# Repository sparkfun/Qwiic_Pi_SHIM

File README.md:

SparkFun Qwiic SHIM for Raspberry Pi
========================================

[*SparkFun Qwiic SHIM for Raspberry Pi (15794)*](https://www.sparkfun.com/products/15794)

A small breakout board to add a qwiic connector to your Raspberry Pi 40pin header. SHIM (Shove Hardware In the Middle).

Repository Contents
-------------------

* **/Hardware** - Eagle design files (.brd, .sch)

Documentation
--------------
* **[Hookup Guide](https://learn.sparkfun.com/tutorials/qwiic-shim-for-raspberry-pi-hookup-guide)** - Basic hookup guide for the SparkFun Qwiic SHIM for Raspberry Pi. 

License Information
-------------------

This product is _**open source**_! 

Please review the LICENSE.md file for license information. 

If you have any questions or concerns on licensing, please contact technical support on our [SparkFun forums](https://forum.sparkfun.com/viewforum.php?f=152).

Distributed as-is; no warranty is given.

- Your friends at SparkFun.

_<COLLABORATION CREDIT>_

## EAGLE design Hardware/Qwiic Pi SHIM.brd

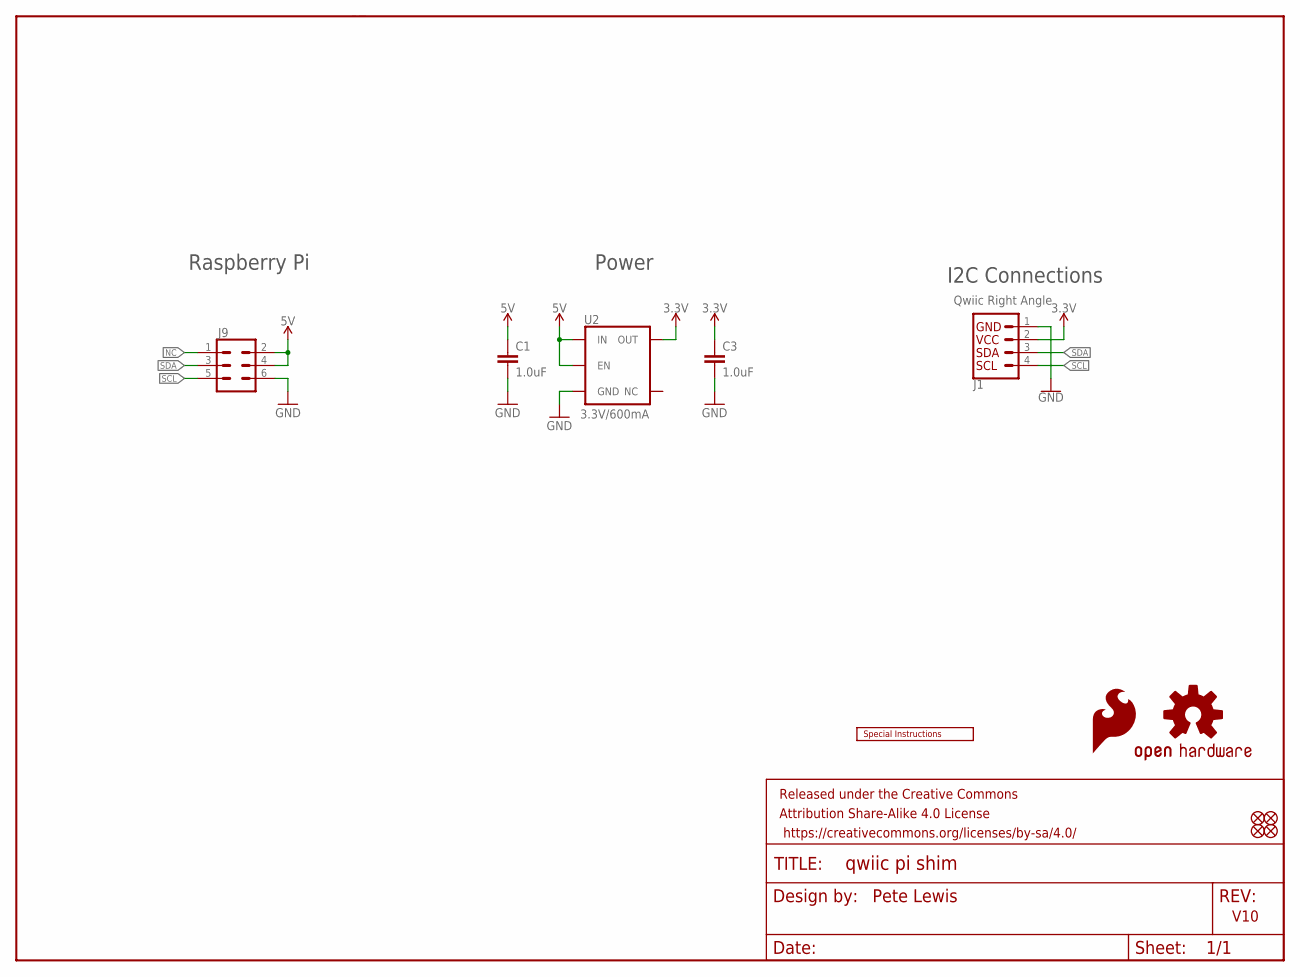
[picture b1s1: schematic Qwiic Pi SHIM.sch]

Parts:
C1, C3: 1.0uF; 0603
FD1, FD2, FD3, FD4: FIDUCIALUFIDUCIAL; FIDUCIAL-MICRO
FRAME1: FRAME-LETTER; CREATIVE_COMMONS
J1: Qwiic Right Angle; 1X04_1MM_RA
J9: SPARKFUN-CONNECTORS_CONN_03X2PISHIM_LOCK_SLOTS; SPARKFUN-CONNECTORS_2X3-NS_PISHIM_LOCKING_SLOTS
LOGO1: OSHW-LOGOMINI; OSHW-LOGO-MINI
U2: 3.3V/600mA; SOT23-5
U$1: SFE_LOGO_FLAME.1_INCH; SFE_LOGO_FLAME_.1
U$4: SPECIAL_INSTRUCTIONS-ORDERING; ORDERING_INSTRUCTIONS

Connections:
3.3V: C3.1, J1.2, U2.5 (OUT)
5V: C1.1, J9.2, J9.4, U2.1 (IN), U2.3 (EN)
GND: C1.2, C3.2, J1.1, J9.6, U2.2 (GND)
NC: J9.1
SCL: J1.4, J9.5
SDA: J1.3, J9.3

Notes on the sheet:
Pete Lewis
Raspberry Pi
V10
I2C Connections
Power

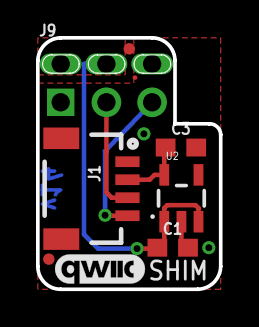
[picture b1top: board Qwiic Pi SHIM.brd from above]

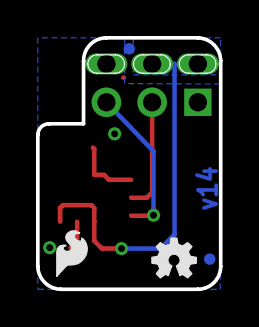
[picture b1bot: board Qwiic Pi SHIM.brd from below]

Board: 2 copper layers, 10.2 x 14.0 mm, 14 parts (4 on the bottom side), 5 nets.

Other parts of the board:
U$3: QWIIC_5MM

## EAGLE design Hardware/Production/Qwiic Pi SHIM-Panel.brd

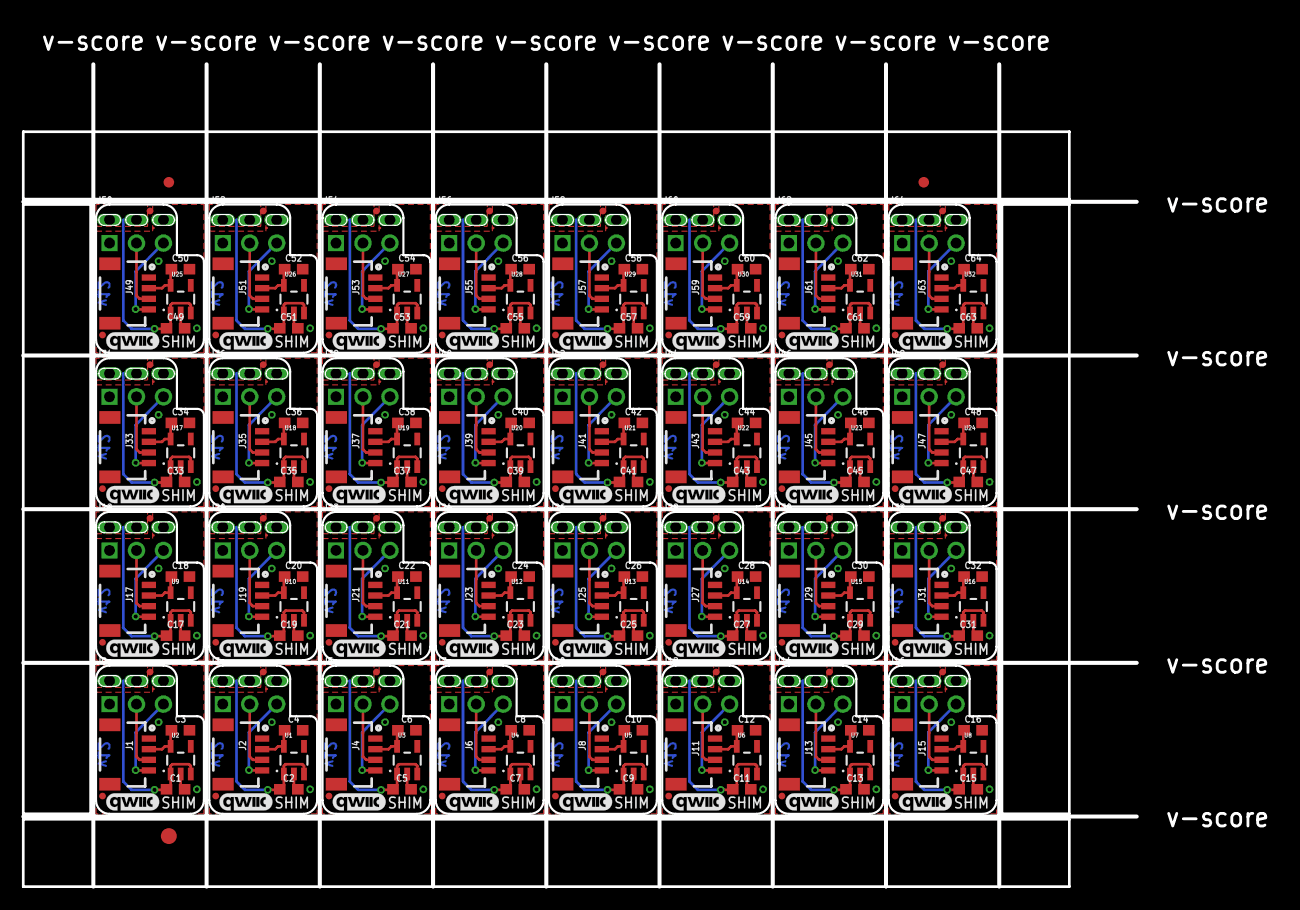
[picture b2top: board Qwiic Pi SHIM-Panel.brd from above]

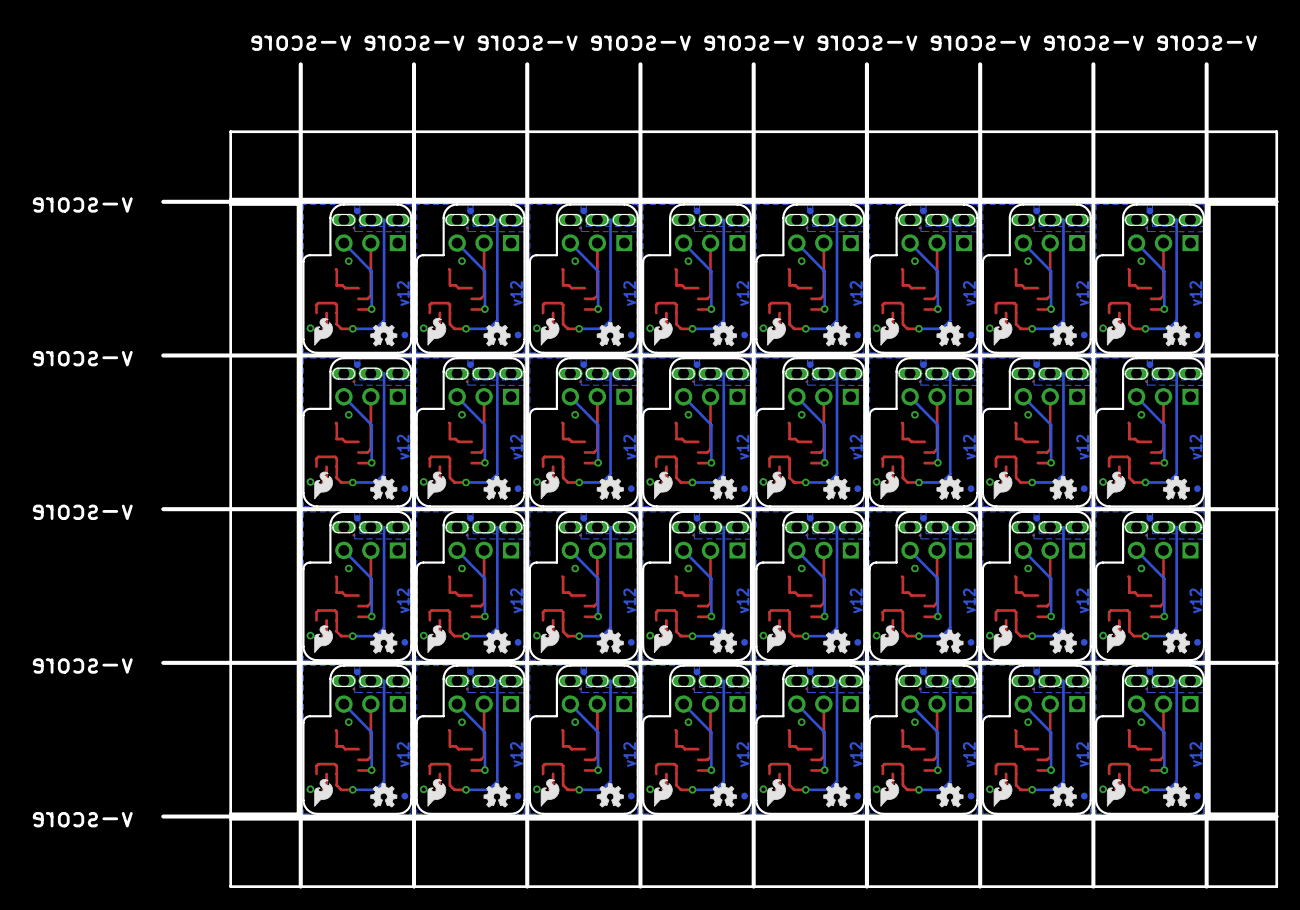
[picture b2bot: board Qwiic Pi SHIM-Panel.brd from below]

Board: 2 copper layers, 118.1 x 81.3 mm, 387 parts (128 on the bottom side), 160 nets.

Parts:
C1, C2, C3, C4, C5, C6, C7, C8, C9, C10, C11, C12, C13, C14, C15, C16, C17, C18, C19, C20, C21, C22, C23, C24, C25, C26, C27, C28, C29, C30, C31, C32, C33, C34, C35, C36, C37, C38, C39, C40, C41, C42, C43, C44, C45, C46, C47, C48, C49, C50, C51, C52, C53, C54, C55, C56, C57, C58, C59, C60, C61, C62, C63, C64: 1.0uF; 0603
E$1, E$2: FIDUCIAL-1X2
E$3: FIDUCIAL-1.5X3
FD1, FD2, FD3, FD4, FD5, FD6, FD7, FD8, FD9, FD10, FD11, FD12, FD13, FD14, FD15, FD16, FD17, FD18, FD19, FD20, FD21, FD22, FD23, FD24, FD25, FD26, FD27, FD28, FD29, FD30, FD31, FD32, FD33, FD34, FD35, FD36, FD37, FD38, FD39, FD40, FD41, FD42, FD43, FD44, FD45, FD46, FD47, FD48, FD49, FD50, FD51, FD52, FD53, FD54, FD55, FD56, FD57, FD58, FD59, FD60, FD61, FD62, FD63, FD64, FD65, FD66, FD67, FD68, FD69, FD70, FD71, FD72, FD73, FD74, FD75, FD76, FD77, FD78, FD79, FD80, FD81, FD82, FD83, FD84, FD85, FD86, FD87, FD88, FD89, FD90, FD91, FD92, FD93, FD94, FD95, FD96, FD97, FD98, FD99, FD100, FD101, FD102, FD103, FD104, FD105, FD106, FD107, FD108, FD109, FD110, FD111, FD112, FD113, FD114, FD115, FD116, FD117, FD118, FD119, FD120, FD121, FD122, FD123, FD124, FD125, FD126, FD127, FD128: FIDUCIALUFIDUCIAL; FIDUCIAL-MICRO
J1, J2, J4, J6, J8, J11, J13, J15, J17, J19, J21, J23, J25, J27, J29, J31, J33, J35, J37, J39, J41, J43, J45, J47, J49, J51, J53, J55, J57, J59, J61, J63: Qwiic Right Angle; 1X04_1MM_RA
J3, J5, J7, J9, J10, J12, J14, J16, J18, J20, J22, J24, J26, J28, J30, J32, J34, J36, J38, J40, J42, J44, J46, J48, J50, J52, J54, J56, J58, J60, J62, J64: SPARKFUN-CONNECTORS_2X3-NS_PISHIM_LOCKING_SLOTS-2MILS
LOGO1, LOGO2, LOGO3, LOGO4, LOGO5, LOGO6, LOGO7, LOGO8, LOGO9, LOGO10, LOGO11, LOGO12, LOGO13, LOGO14, LOGO15, LOGO16, LOGO17, LOGO18, LOGO19, LOGO20, LOGO21, LOGO22, LOGO23, LOGO24, LOGO25, LOGO26, LOGO27, LOGO28, LOGO29, LOGO30, LOGO31, LOGO32: OSHW-LOGOMINI; OSHW-LOGO-MINI
U1, U2, U3, U4, U5, U6, U7, U8, U9, U10, U11, U12, U13, U14, U15, U16, U17, U18, U19, U20, U21, U22, U23, U24, U25, U26, U27, U28, U29, U30, U31, U32: 3.3V/600mA; SOT23-5
U$1, U$2, U$5, U$7, U$9, U$11, U$13, U$15, U$17, U$19, U$21, U$23, U$25, U$27, U$29, U$31, U$33, U$35, U$37, U$39, U$41, U$43, U$45, U$47, U$49, U$51, U$53, U$55, U$57, U$59, U$61, U$63: SFE_LOGO_FLAME.1_INCH; SFE_LOGO_FLAME_.1
U$3, U$4, U$6, U$8, U$10, U$12, U$14, U$16, U$18, U$20, U$22, U$24, U$26, U$28, U$30, U$32, U$34, U$36, U$38, U$40, U$42, U$44, U$46, U$48, U$50, U$52, U$54, U$56, U$58, U$60, U$62, U$64: QWIIC_5MM

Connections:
3.3V: C3.1, J1.2, U2.5
3.3V1: C4.1, J2.2, U1.5
3.3V2: C6.1, J4.2, U3.5
3.3V3: C8.1, J6.2, U4.5
3.3V4: C10.1, J8.2, U5.5
3.3V5: C12.1, J11.2, U6.5
3.3V6: C14.1, J13.2, U7.5
3.3V7: C16.1, J15.2, U8.5
3.3V8: C18.1, J17.2, U9.5
3.3V9: C20.1, J19.2, U10.5
3.3V10: C22.1, J21.2, U11.5
3.3V11: C24.1, J23.2, U12.5
3.3V12: C26.1, J25.2, U13.5
3.3V13: C28.1, J27.2, U14.5
3.3V14: C30.1, J29.2, U15.5
3.3V15: C32.1, J31.2, U16.5
3.3V16: C34.1, J33.2, U17.5
3.3V17: C36.1, J35.2, U18.5
3.3V18: C38.1, J37.2, U19.5
3.3V19: C40.1, J39.2, U20.5
3.3V20: C42.1, J41.2, U21.5
3.3V21: C44.1, J43.2, U22.5
3.3V22: C46.1, J45.2, U23.5
3.3V23: C48.1, J47.2, U24.5
3.3V24: C50.1, J49.2, U25.5
3.3V25: C52.1, J51.2, U26.5
3.3V26: C54.1, J53.2, U27.5
3.3V27: C56.1, J55.2, U28.5
3.3V28: C58.1, J57.2, U29.5
3.3V29: C60.1, J59.2, U30.5
3.3V30: C62.1, J61.2, U31.5
3.3V31: C64.1, J63.2, U32.5
5V: C1.1, J9.2, J9.4, U2.1, U2.3
5V1: C2.1, J3.2, J3.4, U1.1, U1.3
5V2: C5.1, J5.2, J5.4, U3.1, U3.3
5V3: C7.1, J7.2, J7.4, U4.1, U4.3
5V4: C9.1, J10.2, J10.4, U5.1, U5.3
5V5: C11.1, J12.2, J12.4, U6.1, U6.3
5V6: C13.1, J14.2, J14.4, U7.1, U7.3
5V7: C15.1, J16.2, J16.4, U8.1, U8.3
5V8: C17.1, J18.2, J18.4, U9.1, U9.3
5V9: C19.1, J20.2, J20.4, U10.1, U10.3
5V10: C21.1, J22.2, J22.4, U11.1, U11.3
5V11: C23.1, J24.2, J24.4, U12.1, U12.3
5V12: C25.1, J26.2, J26.4, U13.1, U13.3
5V13: C27.1, J28.2, J28.4, U14.1, U14.3
5V14: C29.1, J30.2, J30.4, U15.1, U15.3
5V15: C31.1, J32.2, J32.4, U16.1, U16.3
5V16: C33.1, J34.2, J34.4, U17.1, U17.3
5V17: C35.1, J36.2, J36.4, U18.1, U18.3
5V18: C37.1, J38.2, J38.4, U19.1, U19.3
5V19: C39.1, J40.2, J40.4, U20.1, U20.3
5V20: C41.1, J42.2, J42.4, U21.1, U21.3
5V21: C43.1, J44.2, J44.4, U22.1, U22.3
5V22: C45.1, J46.2, J46.4, U23.1, U23.3
5V23: C47.1, J48.2, J48.4, U24.1, U24.3
5V24: C49.1, J50.2, J50.4, U25.1, U25.3
5V25: C51.1, J52.2, J52.4, U26.1, U26.3
5V26: C53.1, J54.2, J54.4, U27.1, U27.3
5V27: C55.1, J56.2, J56.4, U28.1, U28.3
5V28: C57.1, J58.2, J58.4, U29.1, U29.3
5V29: C59.1, J60.2, J60.4, U30.1, U30.3
5V30: C61.1, J62.2, J62.4, U31.1, U31.3
5V31: C63.1, J64.2, J64.4, U32.1, U32.3
GND: C1.2, C3.2, J1.1, J9.6, U2.2
GND1: C2.2, C4.2, J2.1, J3.6, U1.2
GND2: C5.2, C6.2, J4.1, J5.6, U3.2
GND3: C7.2, C8.2, J6.1, J7.6, U4.2
GND4: C9.2, C10.2, J8.1, J10.6, U5.2
GND5: C11.2, C12.2, J11.1, J12.6, U6.2
GND6: C13.2, C14.2, J13.1, J14.6, U7.2
GND7: C15.2, C16.2, J15.1, J16.6, U8.2
GND8: C17.2, C18.2, J17.1, J18.6, U9.2
GND9: C19.2, C20.2, J19.1, J20.6, U10.2
GND10: C21.2, C22.2, J21.1, J22.6, U11.2
GND11: C23.2, C24.2, J23.1, J24.6, U12.2
GND12: C25.2, C26.2, J25.1, J26.6, U13.2
GND13: C27.2, C28.2, J27.1, J28.6, U14.2
GND14: C29.2, C30.2, J29.1, J30.6, U15.2
GND15: C31.2, C32.2, J31.1, J32.6, U16.2
GND16: C33.2, C34.2, J33.1, J34.6, U17.2
GND17: C35.2, C36.2, J35.1, J36.6, U18.2
GND18: C37.2, C38.2, J37.1, J38.6, U19.2
GND19: C39.2, C40.2, J39.1, J40.6, U20.2
GND20: C41.2, C42.2, J41.1, J42.6, U21.2
GND21: C43.2, C44.2, J43.1, J44.6, U22.2
GND22: C45.2, C46.2, J45.1, J46.6, U23.2
GND23: C47.2, C48.2, J47.1, J48.6, U24.2
GND24: C49.2, C50.2, J49.1, J50.6, U25.2
GND25: C51.2, C52.2, J51.1, J52.6, U26.2
GND26: C53.2, C54.2, J53.1, J54.6, U27.2
GND27: C55.2, C56.2, J55.1, J56.6, U28.2
GND28: C57.2, C58.2, J57.1, J58.6, U29.2
GND29: C59.2, C60.2, J59.1, J60.6, U30.2
GND30: C61.2, C62.2, J61.1, J62.6, U31.2
GND31: C63.2, C64.2, J63.1, J64.6, U32.2
SCL: J1.4, J9.5
SCL1: J2.4, J3.5
SCL2: J4.4, J5.5
SCL3: J6.4, J7.5
SCL4: J8.4, J10.5
SCL5: J11.4, J12.5
SCL6: J13.4, J14.5
SCL7: J15.4, J16.5
SCL8: J17.4, J18.5
SCL9: J19.4, J20.5
SCL10: J21.4, J22.5
SCL11: J23.4, J24.5
SCL12: J25.4, J26.5
SCL13: J27.4, J28.5
SCL14: J29.4, J30.5
SCL15: J31.4, J32.5
SCL16: J33.4, J34.5
SCL17: J35.4, J36.5
SCL18: J37.4, J38.5
SCL19: J39.4, J40.5
SCL20: J41.4, J42.5
SCL21: J43.4, J44.5
SCL22: J45.4, J46.5
SCL23: J47.4, J48.5
SCL24: J49.4, J50.5
SCL25: J51.4, J52.5
SCL26: J53.4, J54.5
SCL27: J55.4, J56.5
SCL28: J57.4, J58.5
SCL29: J59.4, J60.5
SCL30: J61.4, J62.5
SCL31: J63.4, J64.5
SDA: J1.3, J9.3
SDA1: J2.3, J3.3
SDA2: J4.3, J5.3
SDA3: J6.3, J7.3
SDA4: J8.3, J10.3
SDA5: J11.3, J12.3
SDA6: J13.3, J14.3
SDA7: J15.3, J16.3
SDA8: J17.3, J18.3
SDA9: J19.3, J20.3
SDA10: J21.3, J22.3
SDA11: J23.3, J24.3
SDA12: J25.3, J26.3
SDA13: J27.3, J28.3
SDA14: J29.3, J30.3
SDA15: J31.3, J32.3
SDA16: J33.3, J34.3
SDA17: J35.3, J36.3
SDA18: J37.3, J38.3
SDA19: J39.3, J40.3
SDA20: J41.3, J42.3
SDA21: J43.3, J44.3
SDA22: J45.3, J46.3
SDA23: J47.3, J48.3
SDA24: J49.3, J50.3
SDA25: J51.3, J52.3
SDA26: J53.3, J54.3
SDA27: J55.3, J56.3
SDA28: J57.3, J58.3
SDA29: J59.3, J60.3
SDA30: J61.3, J62.3
SDA31: J63.3, J64.3

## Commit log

2019-10-03 Layout complete
2019-10-03 fixed orientation so it goes over the pi
    added ordering instructions - 0.8mm thickness
2019-10-22 Single slot version done
2019-10-23 singel and double slot versions done
2019-10-24 adjusted dimensions to match single to double
    -this lets a small amount of gnd pour around the corner.
    -moved fiductials
    -added gnd vias
2019-10-24 checklist run
    -approve DRC dimension errors, including wire stubbs for double connections on gnd and 5V
2019-10-28 Production files for both signel and double slot versions
2019-11-07 created footprints and variants for 2 mils and 4 mils tighter versions
2019-11-07 Created two more versions to test spacing
    2mil and 4mil spacing (tighter). At this point they are both not proven... PCBs inbound. I'm betting on the 4 mil.
2019-11-18 2 mils tighter version wins - cleaning up repo
    -commiting to the 2 mils tighter version (single slot)
    -deleted all the other prototype versions
    -renamed files to product name (removing the "S2")
2019-12-03 Update README.md
    To template standards
2019-12-05 Fix Hookup Guide Link
    Title
2019-12-05 Update README.md
    Removing link to Fritzing Repo as we do not have a Fritzing part for the Qwiic SHIM.
2020-09-21 corrected image link in readme
2020-09-30 Reverting to tighter spacing (aka v14 or "4MILS")
    -updated single brd files, panel files (and production gerbers)

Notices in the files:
parts and their libraries:
SparkFun-Aesthetics: Licensing: CC v3.0 Share-Alike You are welcome to use this library for commercial purposes.
SparkFun-Connectors: Licensing: Creative Commons ShareAlike 4.0 International - https://creativecommons.org/licenses/by-sa/4.0
SparkFun-Aesthetics: Released under the Creative Commons
